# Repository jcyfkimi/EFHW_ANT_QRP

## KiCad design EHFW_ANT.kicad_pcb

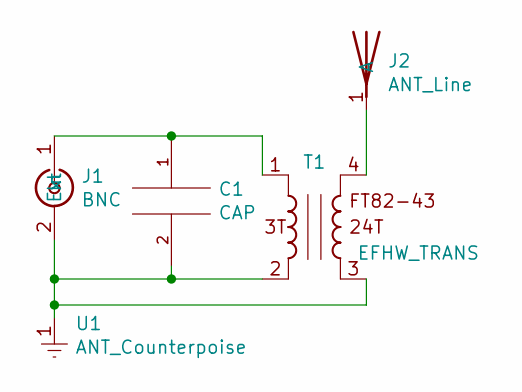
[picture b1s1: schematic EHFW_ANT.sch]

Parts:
C1: CAP; C_Rect_L16.5mm_W7.0mm_P15.00mm_MKT
J1: BNC; BNC_Conn
J2: ANT_Line; EFHW_ANT_Conn
T1: EFHW_TRANS; EFHW_Trans
U1: ANT_Counterpoise; EFHW_ANT_Conn

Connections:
unnamed: C1.1, J1.1 (In), T1.1
unnamed: C1.2, J1.2 (Ext), T1.2, T1.3, U1.1
unnamed: J2.1, T1.4

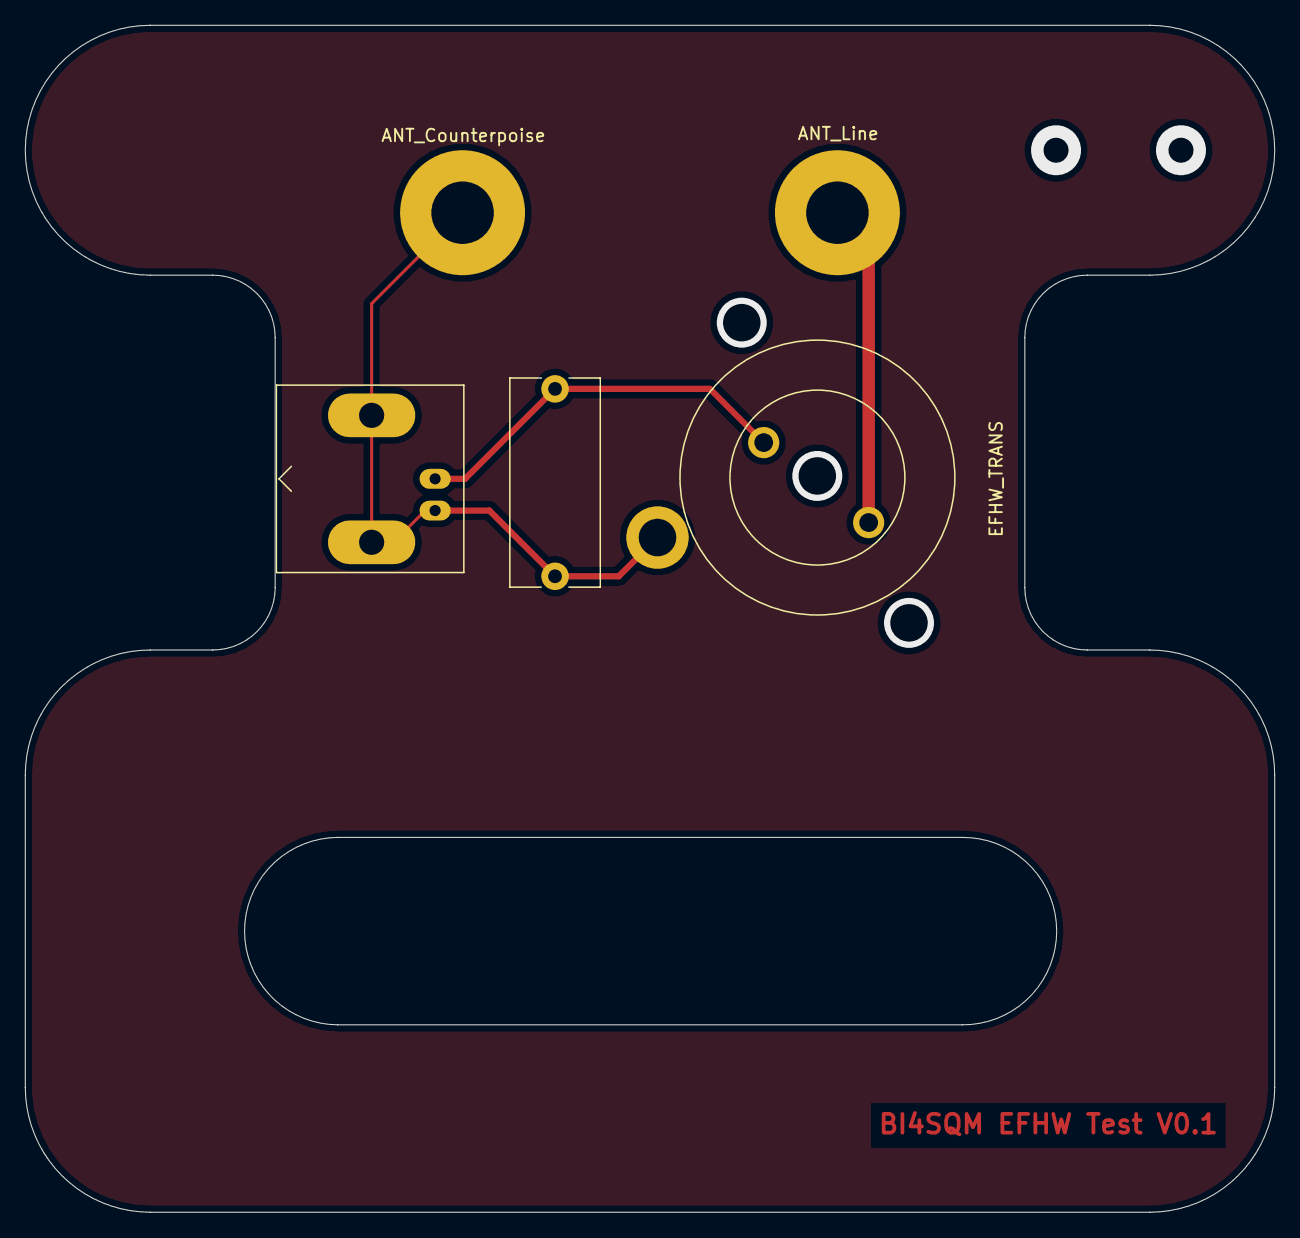
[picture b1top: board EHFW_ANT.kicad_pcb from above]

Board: 2 copper layers, 100.0 x 95.0 mm, 5 parts (0 on the bottom side), 3 nets.
